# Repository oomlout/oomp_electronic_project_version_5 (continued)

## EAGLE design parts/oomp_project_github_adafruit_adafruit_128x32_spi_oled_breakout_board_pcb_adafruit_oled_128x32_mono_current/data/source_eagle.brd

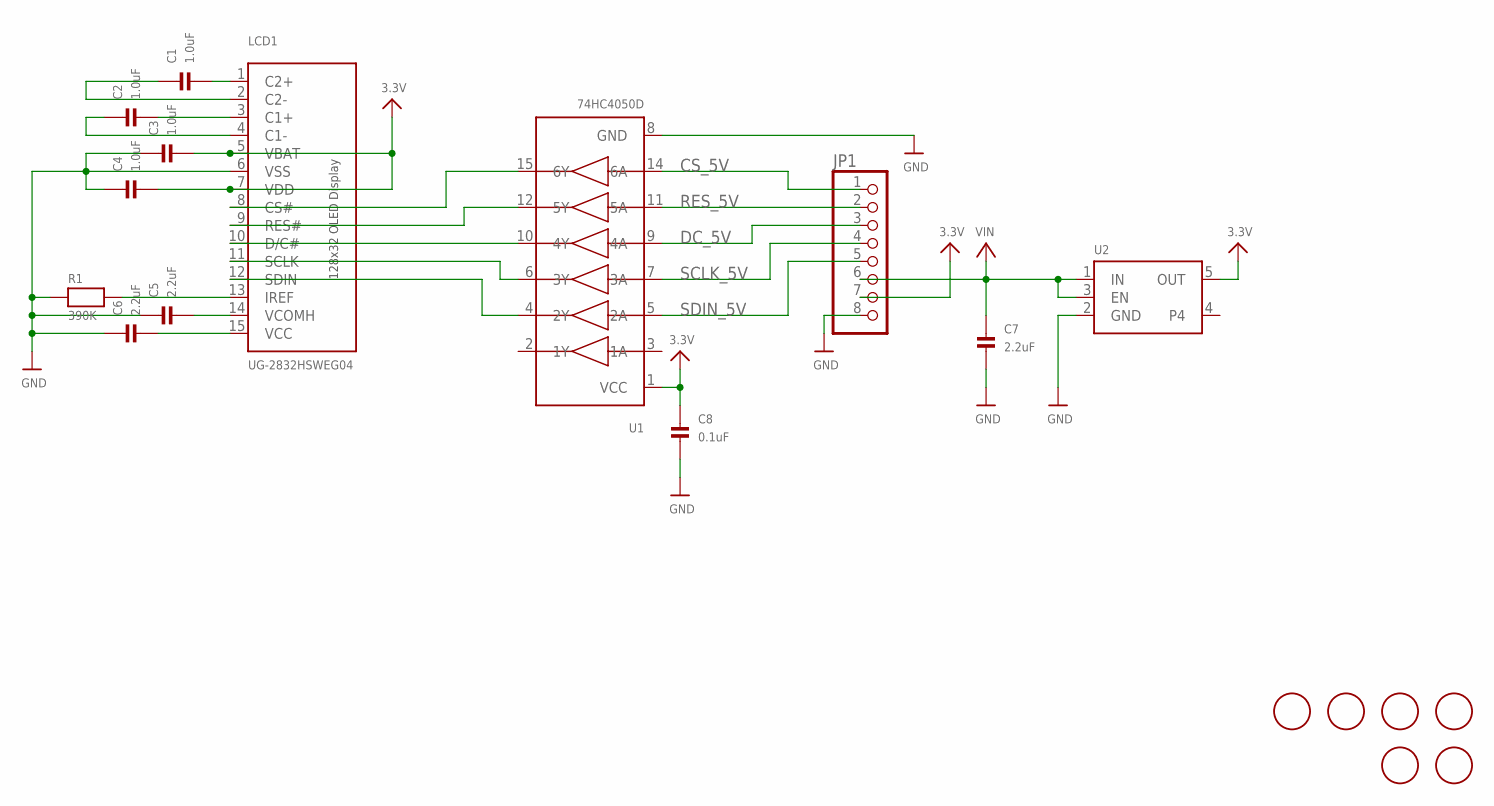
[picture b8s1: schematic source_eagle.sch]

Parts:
C1, C2, C3, C4: 1.0uF; 0805
C5, C6, C7: 2.2uF; 0805
C8: 0.1uF; 0805
JP1: HEADER-1X876MIL; 1X08_ROUND_76
LCD1: UG-2832HSWEG04; UG-2832HSWEG04_WRAPAROUND
R1: 390K; 0805
U1: 74HC4050D; SOIC16
U2: VREG_SOT23-5; SOT23-5
U$2, U$3, U$4, U$5: MOUNTINGHOLE2.0; MOUNTINGHOLE_2.0_PLATED
U$6, U$7: FIDUCIAL; FIDUCIAL_1MM

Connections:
3.3V: C3.2, C4.2, C8.1, JP1.7, LCD1.5 (VBAT), LCD1.7 (VDD), U1.1 (VCC), U2.5 (OUT)
CS_5V: JP1.1, U1.14 (6A)
DC_5V: JP1.3, U1.9 (4A)
GND: C3.1, C4.1, C5.1, C6.1, C7.2, C8.2, JP1.8, LCD1.6 (VSS), R1.1, U1.8 (GND), U2.2 (GND)
unnamed: C1.1, LCD1.2 (C2-)
unnamed: C1.2, LCD1.1 (C2+)
unnamed: C2.1, LCD1.4 (C1-)
unnamed: C2.2, LCD1.3 (C1+)
unnamed: LCD1.8 (CS#), U1.15 (6Y)
unnamed: LCD1.13 (IREF), R1.2
unnamed: C5.2, LCD1.14 (VCOMH)
unnamed: LCD1.9 (RES#), U1.12 (5Y)
unnamed: LCD1.10 (D/C#), U1.10 (4Y)
unnamed: LCD1.11 (SCLK), U1.6 (3Y)
unnamed: LCD1.12 (SDIN), U1.4 (2Y)
unnamed: C6.2, LCD1.15 (VCC)
RES_5V: JP1.2, U1.11 (5A)
SCLK_5V: JP1.4, U1.7 (3A)
SDIN_5V: JP1.5, U1.5 (2A)
VIN: C7.1, JP1.6, U2.1 (IN), U2.3 (EN)

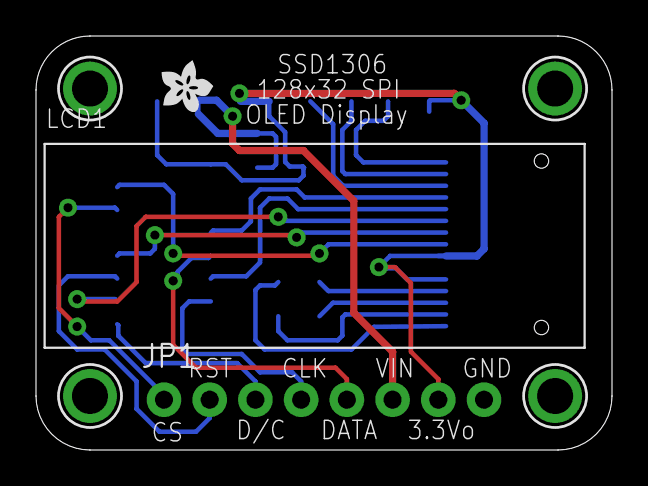
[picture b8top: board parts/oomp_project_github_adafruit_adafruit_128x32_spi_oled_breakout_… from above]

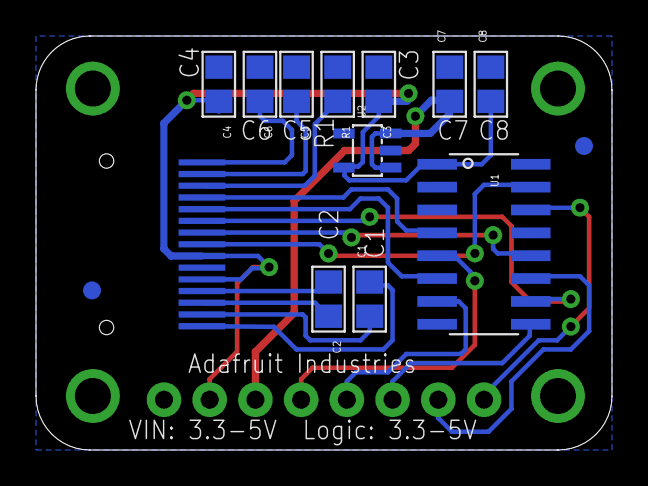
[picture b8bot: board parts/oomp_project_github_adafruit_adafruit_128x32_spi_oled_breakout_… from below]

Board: 2 copper layers, 32.0 x 23.0 mm, 20 parts (13 on the bottom side), 20 nets.

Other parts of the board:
U$10: ADAFRUIT200MIL
